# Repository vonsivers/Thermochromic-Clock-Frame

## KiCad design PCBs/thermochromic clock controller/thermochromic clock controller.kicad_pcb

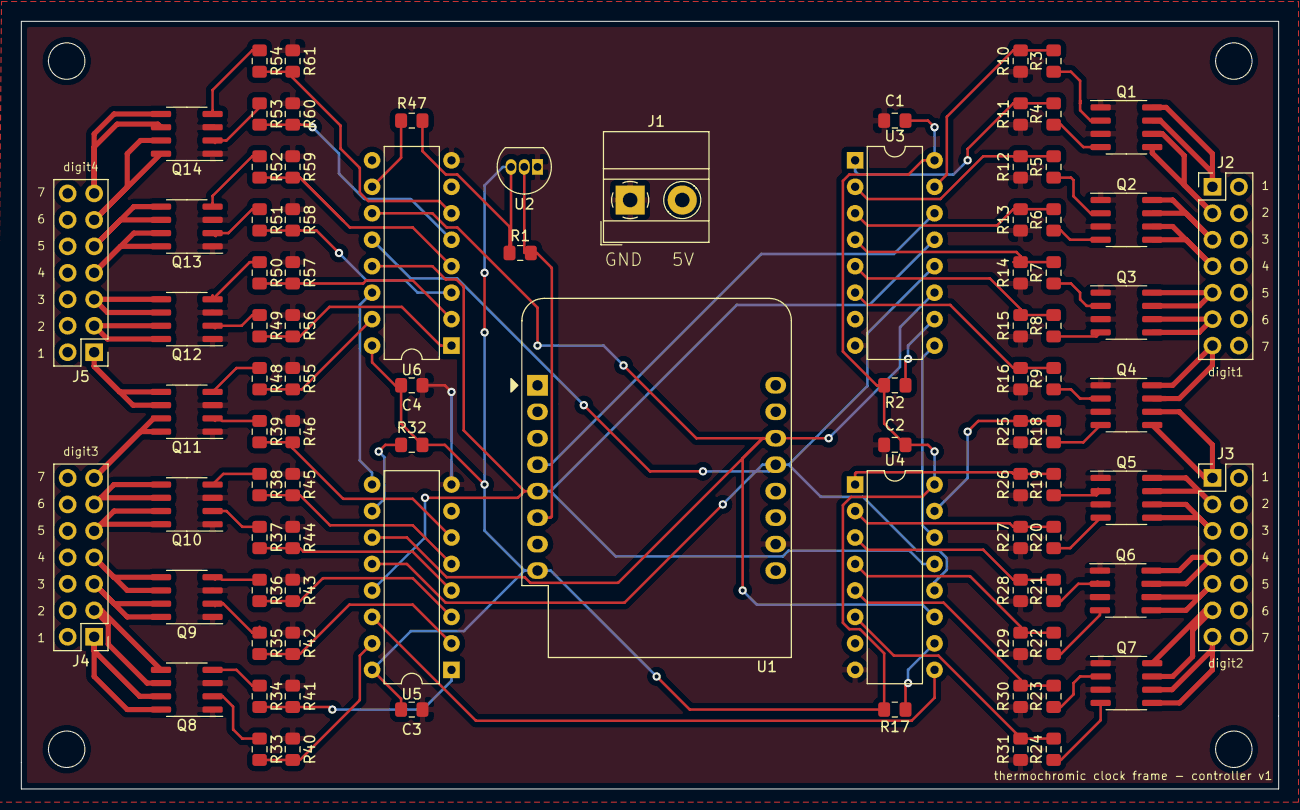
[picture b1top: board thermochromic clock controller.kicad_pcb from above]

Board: 2 copper layers, 120.6 x 73.7 mm, 90 parts (0 on the bottom side), 99 nets.

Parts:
C1, C2, C3, C4: 0.1µF; C_0805_2012Metric_Pad1.15x1.40mm_HandSolder
J1: Screw_Terminal_01x02; TerminalBlock_MetzConnect_Type011_RT05502HBWC_1x02_P5.00mm_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
J2, J3, J4, J5: Conn_02x07_Counter_Clockwise; PinHeader_2x07_P2.54mm_Vertical
Q1, Q2, Q3, Q4, Q5, Q6, Q7, Q8, Q9, Q10, Q11, Q12, Q13, Q14: FDS9926A; SOIC-8_3.9x4.9mm_P1.27mm
R1: 4.7k; R_0805_2012Metric_Pad1.15x1.40mm_HandSolder
R2, R17, R32, R47: 10K; R_0805_2012Metric_Pad1.15x1.40mm_HandSolder
R3, R4, R5, R6, R7, R8, R9, R18, R19, R20, R21, R22, R23, R24, R33, R34, R35, R36, R37, R38, R39, R48, R49, R50, R51, R52, R53, R54: 180R; R_0805_2012Metric_Pad1.15x1.40mm_HandSolder
R10, R11, R12, R13, R14, R15, R16, R25, R26, R27, R28, R29, R30, R31, R40, R41, R42, R43, R44, R45, R46, R55, R56, R57, R58, R59, R60, R61: 10k; R_0805_2012Metric_Pad1.15x1.40mm_HandSolder
U1: WeMos_D1_mini; WEMOS_D1_mini_light
U2: DS18B20; TO-92_Inline
U3, U4, U5, U6: 74HC595; DIP-16_W7.62mm

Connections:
+3V3: C1.1, C2.1, C3.1, C4.1, R1.1, R2.2, R17.2, R32.2, R47.2, U1.8, U2.3, U3.16, U4.16, U5.16, U6.16
+5V: J1.2, J2.2, J2.4, J2.6, J2.8, J2.10, J2.12, J2.14, J3.2, J3.4, J3.6, J3.8, J3.10, J3.12, J3.14, J4.2, J4.4, J4.6, J4.8, J4.10, J4.12, J4.14, J5.2, J5.4, J5.6, J5.8, J5.10, J5.12, J5.14, U1.9
/digit1/SERIN: U1.4, U3.14
/digit2/SERIN: U3.9, U4.14
/digit3/SERIN: U4.9, U5.14
/digit4/SERIN: U5.9, U6.14
ENABLE: U1.5, U3.13, U4.13, U5.13, U6.13
GND: C1.2, C2.2, C3.2, C4.2, J1.1, Q1.1, Q1.3, Q2.1, Q2.3, Q3.1, Q3.3, Q4.1, Q4.3, Q5.1, Q5.3, Q6.1, Q6.3, Q7.1, Q7.3, Q8.1, Q8.3, Q9.1, Q9.3, Q10.1, Q10.3, Q11.1, Q11.3, Q12.1, Q12.3, Q13.1, Q13.3, Q14.1, Q14.3, R10.1, R11.1, R12.1, R13.1, R14.1, R15.1, R16.1, R25.1, R26.1, R27.1, R28.1, R29.1, R30.1, R31.1, R40.1, R41.1, R42.1, R43.1, R44.1, R45.1, R46.1, R55.1, R56.1, R57.1, R58.1, R59.1, R60.1, R61.1, U1.10, U2.1, U3.8, U4.8, U5.8, U6.8
unnamed: J2.1, Q1.7, Q1.8
unnamed: J2.3, Q1.5, Q1.6
unnamed: J2.5, Q2.7, Q2.8
unnamed: J2.7, Q2.5, Q2.6
unnamed: J2.9, Q3.7, Q3.8
unnamed: J2.11, Q3.5, Q3.6
unnamed: J2.13, Q4.7, Q4.8
unnamed: J3.1, Q4.5, Q4.6
unnamed: J3.3, Q5.7, Q5.8
unnamed: J3.5, Q5.5, Q5.6
unnamed: J3.7, Q6.7, Q6.8
unnamed: J3.9, Q6.5, Q6.6
unnamed: J3.11, Q7.7, Q7.8
unnamed: J3.13, Q7.5, Q7.6
unnamed: J4.1, Q8.7, Q8.8
unnamed: J4.3, Q8.5, Q8.6
unnamed: J4.5, Q9.7, Q9.8
unnamed: J4.7, Q9.5, Q9.6
unnamed: J4.9, Q10.7, Q10.8
unnamed: J4.11, Q10.5, Q10.6
unnamed: J4.13, Q11.7, Q11.8
unnamed: J5.1, Q11.5, Q11.6
unnamed: J5.3, Q12.7, Q12.8
unnamed: J5.5, Q12.5, Q12.6
unnamed: J5.7, Q13.7, Q13.8
unnamed: J5.9, Q13.5, Q13.6
unnamed: J5.11, Q14.7, Q14.8
unnamed: J5.13, Q14.5, Q14.6
unnamed: Q1.2, R3.1
unnamed: Q1.4, R4.1
unnamed: Q2.2, R5.1
unnamed: Q2.4, R6.1
unnamed: Q3.2, R7.1
unnamed: Q3.4, R8.1
unnamed: Q4.2, R9.1
unnamed: Q4.4, R18.1
unnamed: Q5.2, R19.1
unnamed: Q5.4, R20.1
unnamed: Q6.2, R21.1
unnamed: Q6.4, R22.1
unnamed: Q7.2, R23.1
unnamed: Q7.4, R24.1
unnamed: Q8.2, R33.1
unnamed: Q8.4, R34.1
unnamed: Q9.2, R35.1
unnamed: Q9.4, R36.1
unnamed: Q10.2, R37.1
unnamed: Q10.4, R38.1
unnamed: Q11.2, R39.1
unnamed: Q11.4, R48.1
unnamed: Q12.2, R49.1
unnamed: Q12.4, R50.1
unnamed: Q13.2, R51.1
unnamed: Q13.4, R52.1
unnamed: Q14.2, R53.1
unnamed: Q14.4, R54.1
unnamed: R1.2, U1.6, U2.2
unnamed: R2.1, U3.10
unnamed: R3.2, R10.2, U3.15
unnamed: R4.2, R11.2, U3.1
unnamed: R5.2, R12.2, U3.2
unnamed: R6.2, R13.2, U3.3
unnamed: R7.2, R14.2, U3.4
unnamed: R8.2, R15.2, U3.5
unnamed: R9.2, R16.2, U3.6
unnamed: R17.1, U4.10
unnamed: R18.2, R25.2, U4.15
unnamed: R19.2, R26.2, U4.1
unnamed: R20.2, R27.2, U4.2
unnamed: R21.2, R28.2, U4.3
unnamed: R22.2, R29.2, U4.4
unnamed: R23.2, R30.2, U4.5
unnamed: R24.2, R31.2, U4.6
unnamed: R32.1, U5.10
unnamed: R33.2, R40.2, U5.15
unnamed: R34.2, R41.2, U5.1
unnamed: R35.2, R42.2, U5.2
unnamed: R36.2, R43.2, U5.3
unnamed: R37.2, R44.2, U5.4
unnamed: R38.2, R45.2, U5.5
unnamed: R39.2, R46.2, U5.6
unnamed: R47.1, U6.10
unnamed: R48.2, R55.2, U6.15
unnamed: R49.2, R56.2, U6.1
unnamed: R50.2, R57.2, U6.2
unnamed: R51.2, R58.2, U6.3
unnamed: R52.2, R59.2, U6.4
unnamed: R53.2, R60.2, U6.5
unnamed: R54.2, R61.2, U6.6
RCK: U1.13, U3.12, U4.12, U5.12, U6.12
SRCK: U1.14, U3.11, U4.11, U5.11, U6.11

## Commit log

2022-03-11 added WiFi manager
